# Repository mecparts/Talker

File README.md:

# General Instrument code to speech board

<br>

<!--https://user-images.githubusercontent.com/2958269/232146398-3386e22a-f2b2-4650-9bee-b34bc73b3b4c.mp4-->
https://user-images.githubusercontent.com/2958269/232169769-99e8073a-7eef-4b14-9e35-29c342e6777a.mp4

<br>

Quoted from [General Instrument Application Note 0505D: CTS256A-AL2 Code-to-Speech Chipset](https://bitsavers.computerhistory.org/components/gi/speech/General_Instrument_-_AN-0505D_-_CTS256A-AL2_Code-to-Speech_Chipset_-_10Dec1986.pdf)

> ## Description
> 
> The Code-to-Speech chip set consists of two chips: the SPO256A-AL2, an
> allophone-based single chip speech synthesizer, and the CTS256A-AL2, an
> 8-bit microcomputer programmed with a letter-to-sound based algorithm.
> This chip set translates English characters into LPC synthesized speech
> sounds.
> 
> ## SPO256-AL2
> 
> The SPO256-AL2 is General Instruments's standard allophone chip and is
> based on the SPO256A speech synthesizer. This synthesizer consists of a
> 10 or 12 pole second-order cascaded LPC filter, a controller, and a
> 16-bit ROM in which 59 allophones (speech sounds) and five pauses are
> stored.
> 
> ## CTS256A-AL2
> 
> The CRT256A-AL2 is a PIC7041 whose on-board ROM is masked with our
> code-to-speech algorithm. This algorithm converts English text (in the
> form of standard ASCII characters) into SPO256A-AL2 compatible allophone
> addresses, using letter-to-sound rules.

I honestly hadn't expected the level of interest that was shown in this
board when I posted it on [r/electronics](https://reddit.com/r/electronics).
So I hadn't prepared a repository. This effort is therefore a little
rushed, and I beg your forgiveness for any obvious in retrospect errors.

## Schematic

The schematic is based largely on the schematics included in the "Technical
Data" sheets that used to be stapled to the back of the Radio Shack
blister packs. They were also included in the Archer Semiconductor Reference
Guides, specifically the [1988 edition](https://archive.org/details/ArcherSemiconductorReferenceGuide1988).

Those schematics appear to have been based in turn on those included in
the aforementioned GI Application Note.

Since I wasn't expecting anyone else to want to use this, I've customised
the schematic to suit myself. There's no parallel port interface, and the
serial interface is programmed not by onboard DIP switches, but by the
contents of the exception word EPROM.

The active filter was cribbed directly from David C. Alford's article
in the [December 1985 issue of Micro Cornucopia, "Speech Generation With Radio Shack's SPO256"](https://archive.org/details/micro-cornucopia-magazine-1985-12).
Although I seemed to have it working well enough when I breadboarded the
circuit, the first version on the PCB was pretty horrible. It sounded like
it was clipping - a lot. It turned out to be a dumb mistake on my part.
Just because the LM324 is spec'd to work on a single supply, the circuit
wasn't designed for that. Without a negative supply, I was losing the 
entire negative half of the signal. How on earth I didn't hear that on
the breadboarded version, I have no idea. I toyed with the idea of 
pulling V- from the MAX232A and regulating it down to -5V; the current
requirements of the LM324 were modest enough I could have gotten away
with it. But I couldn't quickly find a through hole negative regulator
that didn't draw much more current than the LM324 would have. I had a
few ICL7660s in my parts box, so I went that route instead.

# The PCB

The board layout was inspired by the [CTS256A-AL2 Text-To-Speech Board](https://www.smbaker.com/cts256a-al2-text-to-speech-board).
It wasn't until I saw that one a couple of years back that I realized that
my oh-so-much-larger solderless breadboard version could be tamed into
something more reasonably sized.

In the [gerbers subdirectory](gerbers/), you'll find all the Gerber
files, as well as a zipped compilation suitable for submitting to
[JLCPCB](https://jlcpcb.com/), which is where I had my boards made.

# Parts List

Sch/PCB #|Detail
---------|------
U1|CTS256A-AL2 DIP40 600 mil
U2|74ALS573 DIP20 300 mil
U3|74LS138 DIP16 300 mil
U4|SP0256A-AL2 DIP28 600 mil
U5|LM324 DIP14 300 mil
U6|LM386 DIP8 300 mil
U7|MAX232 DIP16 300 mil
U8|74LS14 DIP14 300 mil
U9|ICL7660 DIP8 300 mil
U10|2716/32 2K/4Kx8 EPROM DIP24 600 mil
U11|6116 2Kx8 SRAM DIP24 600 mil
Y1|10MHz crystal HC49-U
Y2|3.12MHz crystal HC49-U (3.58MHz color burst crytal will work)
R1,R14,<br>R15|10K 1/8W
R13|10 ohms 1/8W
R16,17|1K 1/8W
R18|20K 1/8W
R2,5,12|4.7K 1/8W
RN1|4.7K bussed resistor array (DigiKey# 4607X-101-472LF-ND)
C1,C2,C3,<br>C5,C13,<br>C20-C29|100nF ceramic capcitors, 0.1" lead spacing
C10,C11,C31|10uF electrolytic capacitors, 2mm lead spacing
C16|22nF ceramic capacitor, 0.1" lead spacing
C4,C8|220uF electrolytic capacitors, 2.5mm lead spacing
C6,C7,<br>C14,C15|22pF ceramic capacitors, 2.5mm lead spacing
C9,C12,<br>C17,C18,<br>C19|47nF ceramic capacitors, 2.5mm lead spacing
C31|2.2uF tantalum capacitor, 0.1" lead spacing
D1|3mm LED
J1|DC Barrel 2.1mm Jack
J2|DSUB-9 Female Horizontal (Assmann A-DF 09 A-KG-T2S)
J3|3.5mm audio jack(CUI SJ1-3544)
J4|2 pin header, vertical, 0.1" lead spacing
J5|Molex KK-254 AE-6410-02A 2 pin header, 0.1" lead spacing
J6|3 pin header, vertical, 0.1" lead spacing
P1|10K audio taper pot (Bourns PTV111-1415A-A103)
SW1|SPST 6mm sq. tactile switch (CUI TS02-66-60-BK-100-LCR-D)

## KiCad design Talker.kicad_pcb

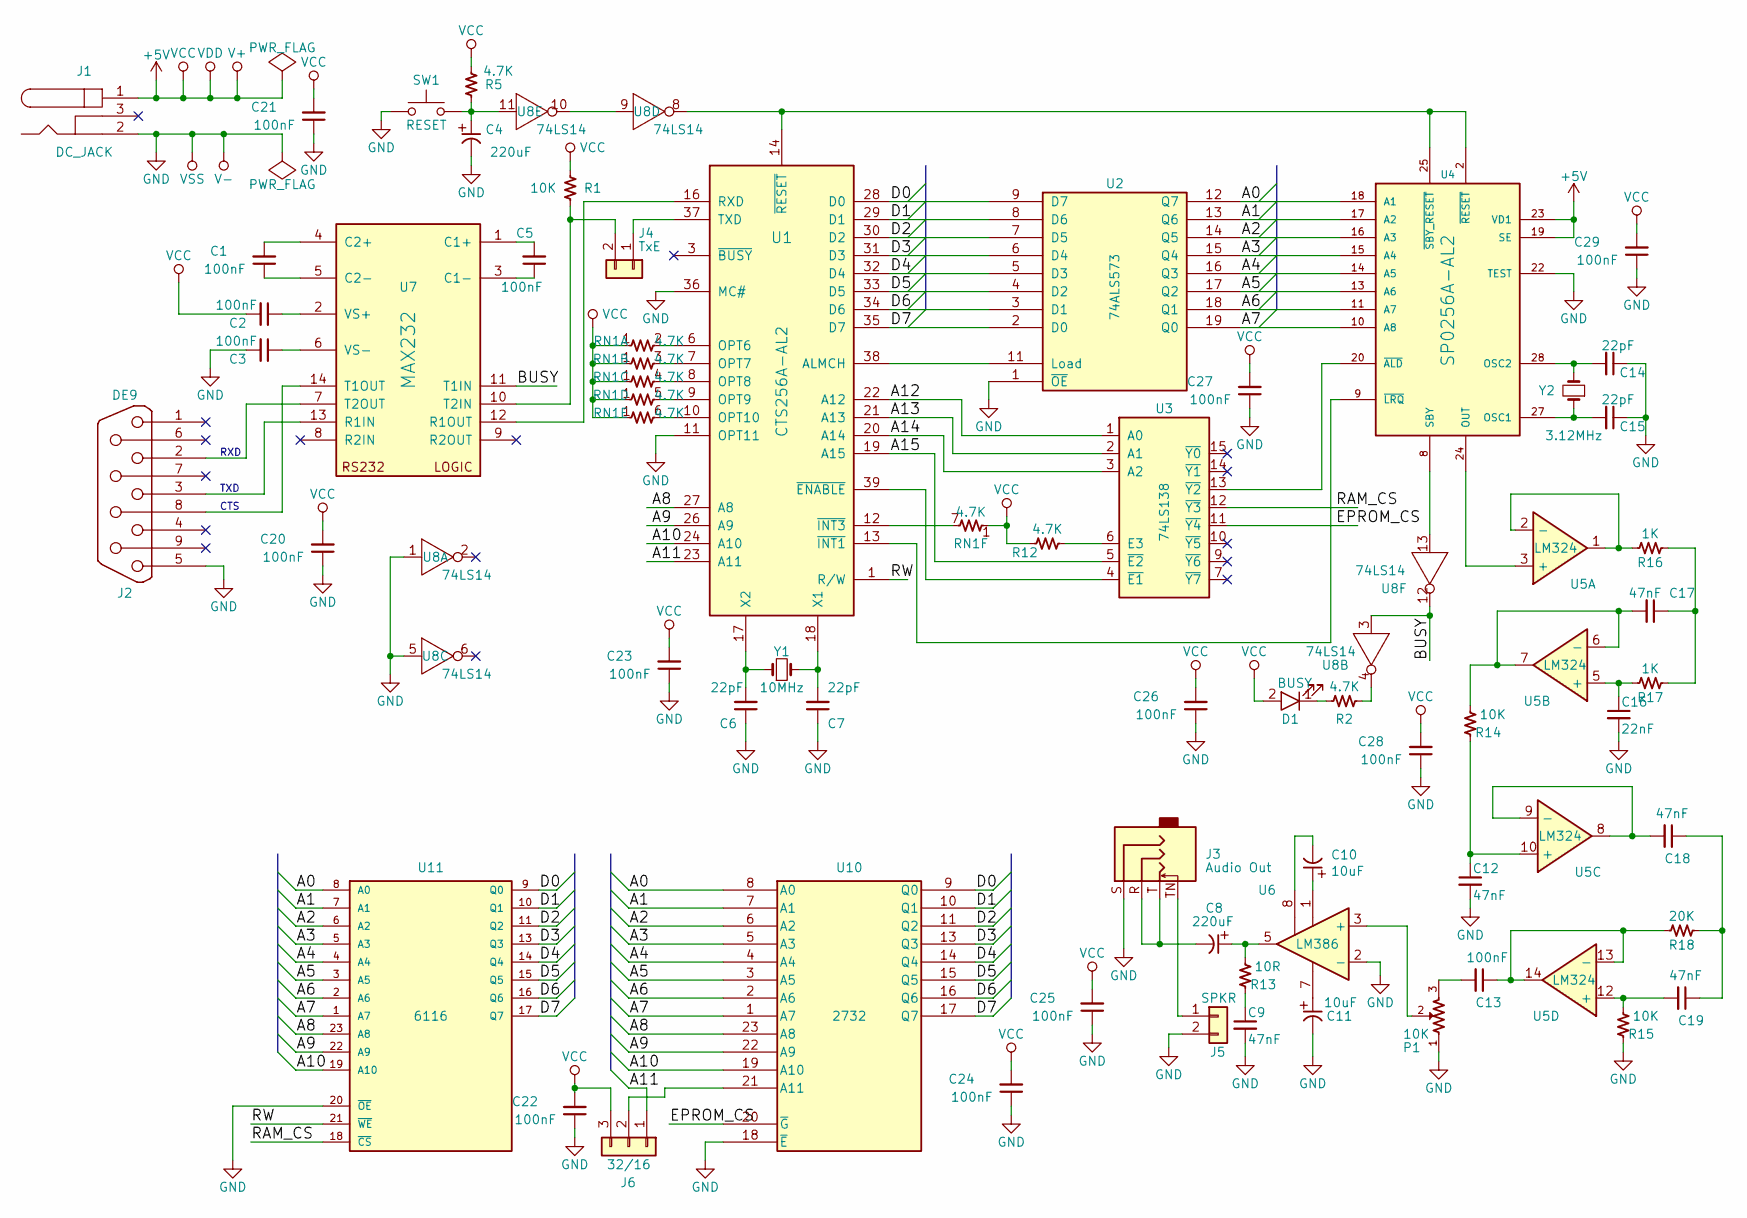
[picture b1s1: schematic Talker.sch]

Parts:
C1, C2, C3, C5, C13, C20, C21, C22, C23, C24, C25, C26, C27, C28, C29: 100nF; C_Disc_D3_P2.5
C4, C8: 220uF; CP_Radial_D6.3mm_P2.50mm
C6, C7, C14, C15: 22pF; C_Disc_D3_P2.5
C9, C12, C17, C18, C19: 47nF; C_Disc_D3_P2.5
C10, C11: 10uF; CP_Radial_D5.0mm_P2.00mm
C16: 22nF; C_Disc_D3_P2.5
D1: BUSY; LED-3MM
J1: DC_JACK; BarrelJack_Horizontal
J2: DE9; DSUB-9_Female_Horizontal_Assmann_A-DF_09_A-KG-T2S
J3: Audio Out; Jack_3.5mm_CUI_SJ1-3544_Horizontal
J4: TxE; PinHeader_1x02_P2.54mm_Vertical
J5: SPKR; Molex_KK-254_AE-6410-02A_1x02_P2.54mm_Vertical
J6: 32/16; PinHeader_1x03_P2.54mm_Vertical
P1: 10K; Potentiometer_Bourns_PTV111-1_Single_Horizontal
R1, R14, R15: 10K; R3
R2, R5, R12: 4.7K; R3
R13: 10R; R3
R16, R17: 1K; R3
R18: 20K; R3
RN1: 4.7K; R_Array_SIP7
SW1: RESET; SW_PUSH_6mm
U1: CTS256A-AL2; DIP-40_W15.24mm_LongPads
U2: 74ALS573; DIP-20_W7.62mm_LongPads
U3: 74LS138; DIP-16_W7.62mm_LongPads
U4: SP0256A-AL2; DIP-28_W15.24mm_LongPads
U5: LM324; DIP-14_W7.62mm_LongPads
U6: LM386; DIP-8_W7.62mm_LongPads
U7: MAX232; DIP-16_W7.62mm_LongPads
U8: 74LS14; DIP-14_W7.62mm_LongPads
U10: 2732; DIP-24_W15.24mm_LongPads
U11: 6116; DIP-24_W15.24mm_LongPads
Y1: 10MHz; Crystal_HC49-U_Vertical
Y2: 3.12MHz; Crystal_HC49-U_Vertical

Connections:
+5V: C2.2, C20.2, C21.2, C22.2, C23.2, C24.2, C25.2, C26.2, C27.2, C28.2, C29.2, D1.2 (A), J1.1, J6.3, R1.1, R5.1, R12.2, RN1.1 (R1.1), U1.25 (VDD), U2.20 (VCC), U3.16 (VCC), U4.7 (VDD), U4.19 (SE), U4.23 (VD1), U5.4 (V+), U6.6 (V+), U7.16 (VCC), U8.14 (VCC), U10.24 (VCC), U11.24 (VCC); also elsewhere on the board
/A0: U2.12 (Q7), U4.18 (A1), U10.8 (A0), U11.8 (A0)
/A1: U2.13 (Q6), U4.17 (A2), U10.7 (A1), U11.7 (A1)
/A2: U2.14 (Q5), U4.16 (A3), U10.6 (A2), U11.6 (A2)
/A3: U2.15 (Q4), U4.15 (A4), U10.5 (A3), U11.5 (A3)
/A4: U2.16 (Q3), U4.14 (A5), U10.4 (A4), U11.4 (A4)
/A5: U2.17 (Q2), U4.13 (A6), U10.3 (A5), U11.3 (A5)
/A6: U2.18 (Q1), U4.11 (A7), U10.2 (A6), U11.2 (A6)
/A7: U2.19 (Q0), U4.10 (A8), U10.1 (A7), U11.1 (A7)
/A8: U1.27 (A8), U10.23 (A8), U11.23 (A8)
/A9: U1.26 (A9), U10.22 (A9), U11.22 (A9)
/A10: U1.24 (A10), U10.19 (A10), U11.19 (A10)
/A11: J6.1, U1.23 (A11)
/A12: U1.22 (A12), U3.1 (A0)
/A13: U1.21 (A13), U3.2 (A1)
/A14: U1.20 (A14), U3.3 (A2)
/A15: U1.19 (A15), U3.5 (~E2)
/BUSY: U7.11 (T1IN), U8.3, U8.12
/D0: U1.28 (D0), U2.9 (D7), U10.9 (Q0), U11.9 (Q0)
/D1: U1.29 (D1), U2.8 (D6), U10.10 (Q1), U11.10 (Q1)
/D2: U1.30 (D2), U2.7 (D5), U10.11 (Q2), U11.11 (Q2)
/D3: U1.31 (D3), U2.6 (D4), U10.13 (Q3), U11.13 (Q3)
/D4: U1.32 (D4), U2.5 (D3), U10.14 (Q4), U11.14 (Q4)
/D5: U1.33 (D5), U2.4 (D2), U10.15 (Q5), U11.15 (Q5)
/D6: U1.34 (D6), U2.3 (D1), U10.16 (Q6), U11.16 (Q6)
/D7: U1.35 (D7), U2.2 (D0), U10.17 (Q7), U11.17 (Q7)
/EPROM_CS: U3.11 (~Y4), U10.20 (~G)
/RAM_CS: U3.12 (~Y3), U11.18 (~CS)
/RW: U1.1 (R/W), U11.21 (~WE)
GND: C3.2, C4.2, C6.1, C7.1, C9.2, C11.2, C12.2, C14.1, C15.1, C16.2, C20.1, C21.1, C22.1, C23.1, C24.1, C25.1, C26.1, C27.1, C28.1, C29.1, J1.2, J2.5, J3.S, J5.2, P1.1, R15.2, SW1.1, U1.11 (OPT11), U1.36 (MC#), U1.40 (VSS), U2.1 (~OE), U2.10 (GND), U3.8 (GND), U4.1 (VSS), U4.22 (TEST), U6.2 (-), U6.4 (GND), U7.15 (GND), U8.1, U8.5, U8.7 (GND), U10.12 (GND), U10.18 (~E), U11.12 (GND), U11.20 (~OE); also elsewhere on the board
unnamed: C1.1, U7.5 (C2-)
unnamed: C1.2, U7.4 (C2+)
unnamed: C2.1, U7.2 (VS+)
unnamed: C3.1, U7.6 (VS-)
unnamed: C4.1, R5.2, SW1.2, U8.11
unnamed: C5.1, U7.3 (C1-)
unnamed: C5.2, U7.1 (C1+)
unnamed: C6.2, U1.17 (X2), Y1.1
unnamed: C7.2, U1.18 (X1), Y1.2
unnamed: C8.1, R13.1, U6.5
unnamed: C8.2, J3.R, J3.T
unnamed: C9.1, R13.2
unnamed: C11.1, U6.7
unnamed: C12.1, R14.2, U5.10 (+)
unnamed: C13.1, R18.2, U5.13 (-), U5.14
unnamed: C13.2, P1.3
unnamed: C14.2, U4.28 (OSC2), Y2.2
unnamed: C15.2, U4.27 (OSC1), Y2.1
unnamed: C16.1, R17.2, U5.5 (+)
unnamed: C17.1, R16.1, R17.1
unnamed: C17.2, R14.1, U5.6 (-), U5.7
unnamed: C18.1, C19.1, R18.1
unnamed: C18.2, U5.8, U5.9 (-)
unnamed: C19.2, R15.1, U5.12 (+)
unnamed: D1.1 (K), R2.2
unnamed: J2.2, U7.7 (T2OUT)
unnamed: J2.3, U7.13 (R1IN)
unnamed: J2.8, U7.14 (T1OUT)
unnamed: J3.TN, J5.1
unnamed: J4.1, U1.37 (TXD)
unnamed: J4.2, R1.2, U7.10 (T2IN)
unnamed: J6.2, U10.21 (A11)
unnamed: P1.2, U6.3 (+)
unnamed: R2.1, U8.4
unnamed: R12.1, U3.6 (E3)
unnamed: R16.2, U5.1, U5.2 (-)
unnamed: RN1.2 (R1.2), U1.6 (OPT6)
unnamed: RN1.3 (R1.2), U1.7 (OPT7)
unnamed: RN1.4 (R1.2), U1.8 (OPT8)
unnamed: RN1.5 (R1.2), U1.9 (OPT9)
unnamed: RN1.6 (R1.2), U1.10 (OPT10)
unnamed: RN1.7 (R1.2), U1.12 (~INT3)
unnamed: U1.13 (~INT1), U4.9 (~LRQ)
unnamed: U1.14 (~RESET), U4.2 (~RESET), U4.25 (~SBY_RESET), U8.8
unnamed: U1.16 (RXD), U7.12 (R1OUT)
unnamed: U1.38 (ALMCH), U2.11 (Load)
unnamed: U1.39 (~ENABLE), U3.4 (~E1)
unnamed: U3.13 (~Y2), U4.20 (~ALD)
unnamed: U4.8 (SBY), U8.13
unnamed: U4.24 (OUT), U5.3 (+)
unnamed: U8.9, U8.10
V-: U5.11 (V-); also elsewhere on the board

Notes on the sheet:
RXD
TXD
CTS

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
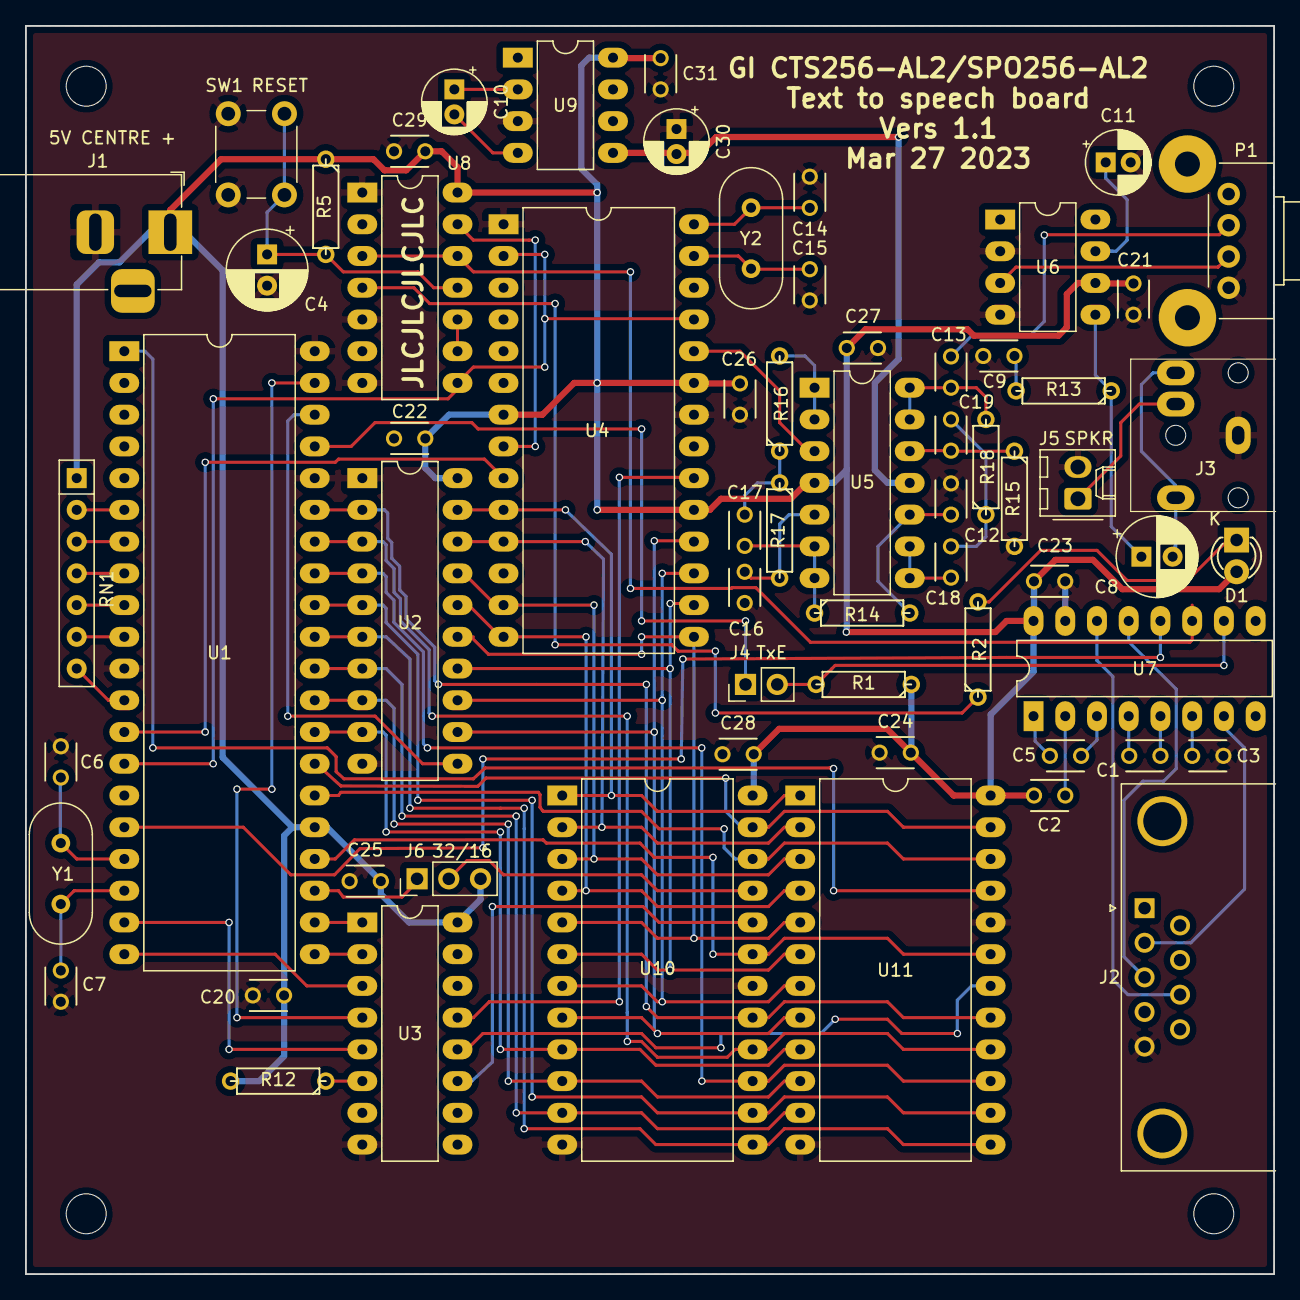
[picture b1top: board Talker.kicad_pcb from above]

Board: 2 copper layers, 99.9 x 99.9 mm, 64 parts (0 on the bottom side), 84 nets.

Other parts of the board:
C30: 10uF; CP_Radial_D5.0mm_P2.00mm
C31: 2.2uF; C_Disc_D3_P2.5
U9: ICL7660; DIP-8_W7.62mm_LongPads

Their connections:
+5V: C31.2, U9.8; also elsewhere on the board
GND: C30.1, C31.1, U9.3; also elsewhere on the board
V-: C30.2, U9.5; also elsewhere on the board

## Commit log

2023-02-19 Added unlicense file
2023-02-19 Added schematic PNG
2023-02-19 Added EPROM hex file
2023-02-19 Added initial readme and picture
2023-02-19 Tweaking readme
2023-02-19 Added video to readme
2023-02-19 Minor formatting tweak to readme
2023-02-19 Fixing more formatting in readme
2023-04-14 Modified the circuit to add a negative supply for the op-amp. It made a world of difference!
2023-04-14 Updated the demo video
2023-04-14 Updated board image
2023-04-14 Added board image
    (since MP4 video nor thumbnail seems to be working... odd)
2023-04-14 Ironing out the video wrinkle
    Use H264 rather than MPEG-4 and cross fingers
